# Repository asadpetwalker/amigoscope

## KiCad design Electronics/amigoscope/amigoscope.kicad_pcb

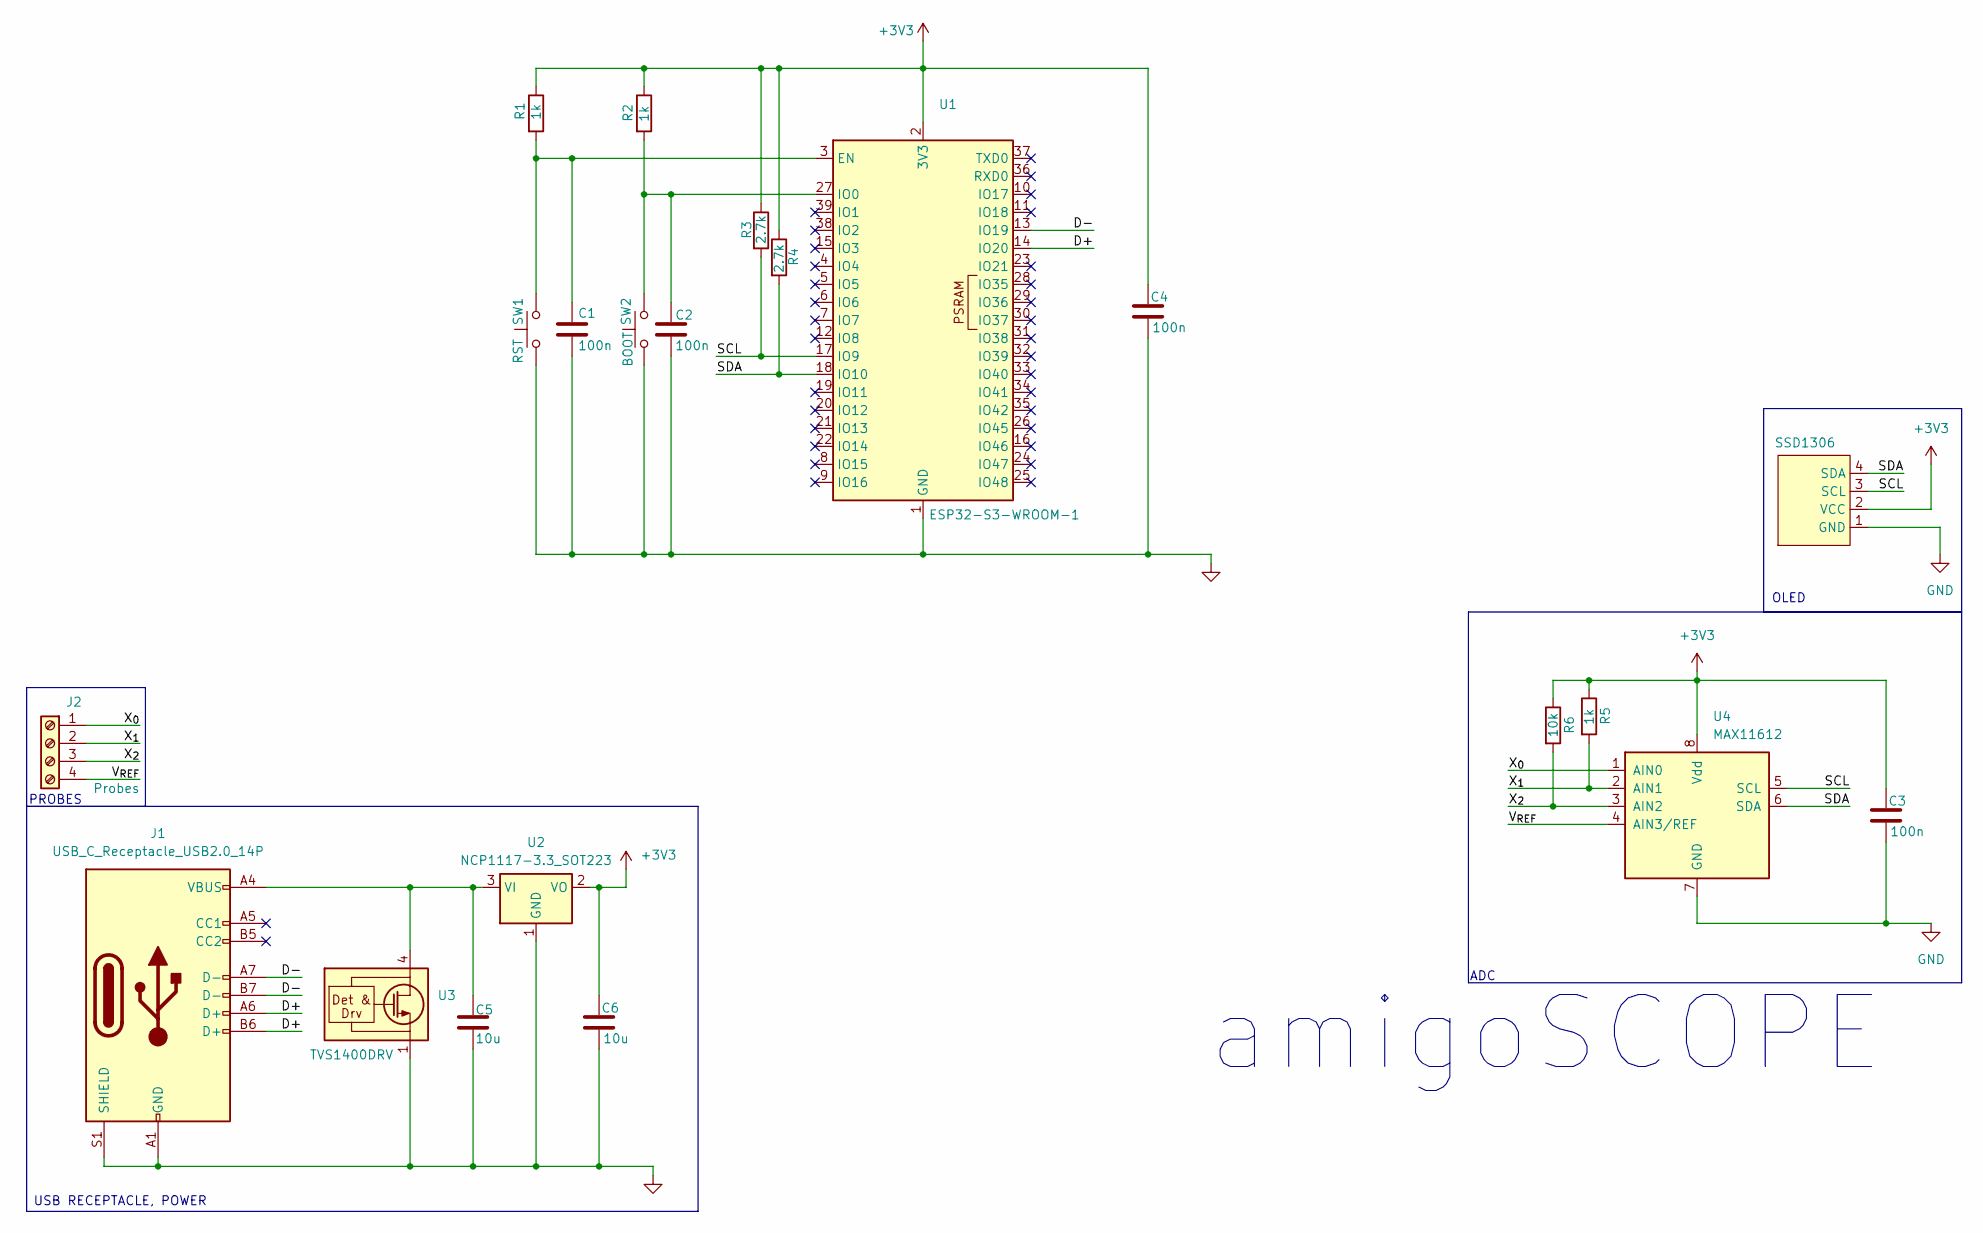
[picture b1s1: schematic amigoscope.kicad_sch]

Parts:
C1, C2, C3, C4: 100n; C_0805_2012Metric
C5, C6: 10u; C_0805_2012Metric
J1: USB_C_Receptacle_USB2.0_14P; USB_C_Receptacle_GCT_USB4105-xx-A_16P_TopMnt_Horizontal
J2: Probes; TerminalBlock_Phoenix_PT-1,5-4-3.5-H_1x04_P3.50mm_Horizontal
R1, R2, R5: 1k; R_0603_1608Metric
R3, R4: 2.7k; R_0603_1608Metric
R6: 10k; R_0603_1608Metric
SSD1306: PinSocket_1x04_P2.54mm_Vertical
SW1: RST; SW_Push_1P1T_NO_CK_KMR2
SW2: BOOT; SW_Push_1P1T_NO_CK_KMR2
U1: ESP32-S3-WROOM-1
U2: NCP1117-3.3_SOT223; SOT-223-3_TabPin2
U3: TVS1400DRV; WSON-6-1EP_2x2mm_P0.65mm_EP1x1.6mm
U4: MAX11612; MSOP-8_3x3mm_P0.65mm

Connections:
+3V3: C3.1, C4.1, C6.1, R1.1, R2.1, R3.1, R4.1, R5.1, R6.1, SSD1306.2 (VCC), U1.2 (3V3), U2.2 (VO), U4.8 (Vdd)
/D+: J1.A6 (D+), J1.B6 (D+), U1.14 (IO20)
/D-: J1.A7 (D-), J1.B7 (D-), U1.13 (IO19)
/SCL: R3.2, SSD1306.3 (SCL), U1.17 (IO9), U4.5 (SCL)
/SDA: R4.2, SSD1306.4 (SDA), U1.18 (IO10), U4.6 (SDA)
/V_{REF}: J2.4, U4.4 (AIN3/REF)
/X_{0}: J2.1, U4.1 (AIN0)
/X_{1}: J2.2, R5.2, U4.2 (AIN1)
/X_{2}: J2.3, R6.2, U4.3 (AIN2)
GND: C1.2, C2.2, C3.2, C4.2, C5.2, C6.2, J1.A1 (GND), J1.A12 (GND), J1.B1 (GND), J1.B12 (GND), J1.S1 (SHIELD), SSD1306.1 (GND), SW1.1, SW2.1, U1.1 (GND), U1.40 (GND), U1.41 (GND), U2.1 (GND), U3.1 (GND), U3.2 (GND), U3.3 (GND), U3.7 (GND), U4.7 (GND)
unnamed: C1.1, R1.2, SW1.2, U1.3 (EN)
unnamed: C2.1, R2.2, SW2.2, U1.27 (IO0)
unnamed: C5.1, J1.A4 (VBUS), J1.A9 (VBUS), J1.B4 (VBUS), J1.B9 (VBUS), U2.3 (VI), U3.4 (IN), U3.5 (IN), U3.6 (IN)

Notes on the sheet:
amigoSCOPE
PROBES
ADC
USB RECEPTACLE, POWER
OLED

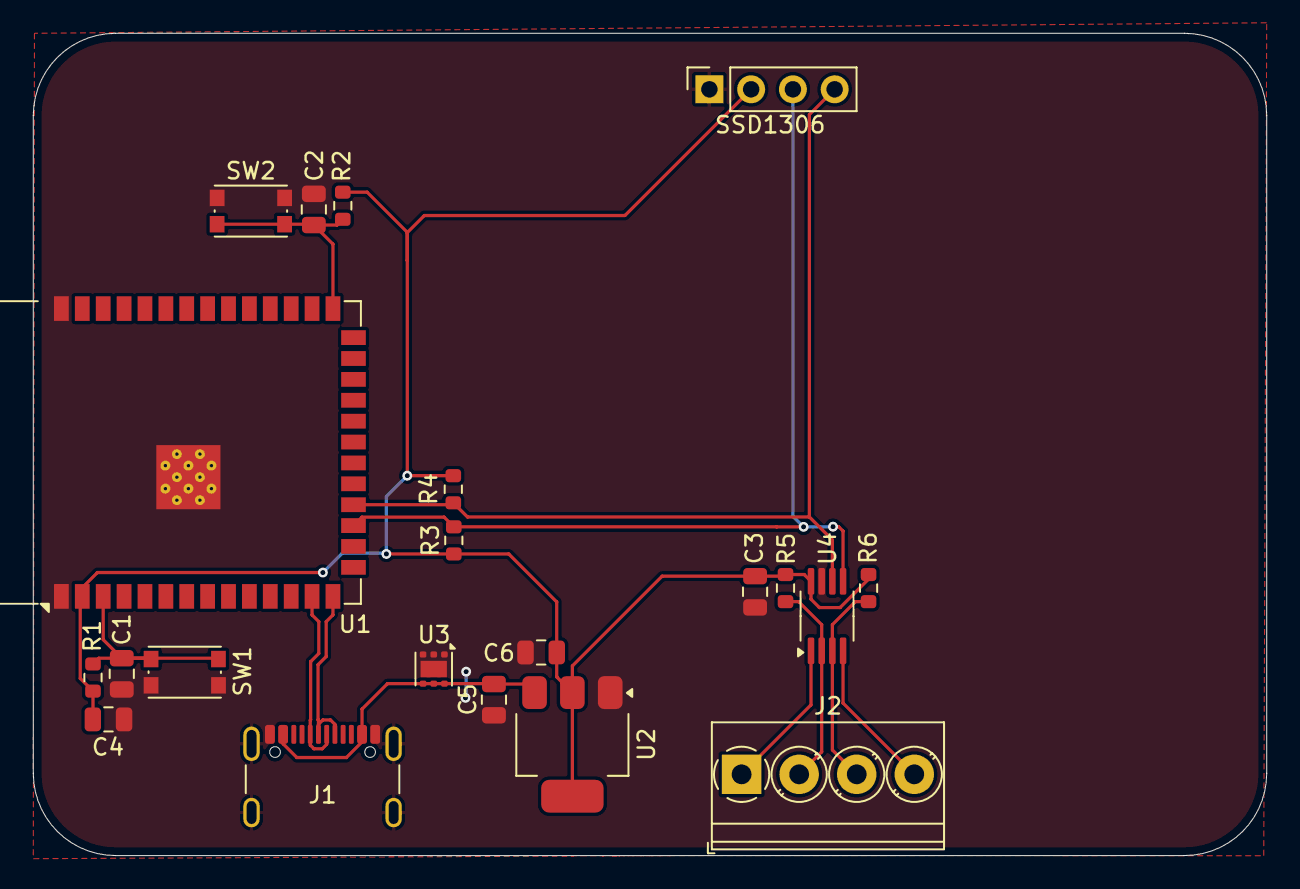
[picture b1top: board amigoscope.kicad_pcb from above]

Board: 2 copper layers, 75.0 x 50.0 mm, 21 parts (0 on the bottom side), 13 nets.

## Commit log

2026-02-20 basic amigoscope
2026-02-20 finished amigoscope schematic + starting pcb
2026-02-20 finished pcb
